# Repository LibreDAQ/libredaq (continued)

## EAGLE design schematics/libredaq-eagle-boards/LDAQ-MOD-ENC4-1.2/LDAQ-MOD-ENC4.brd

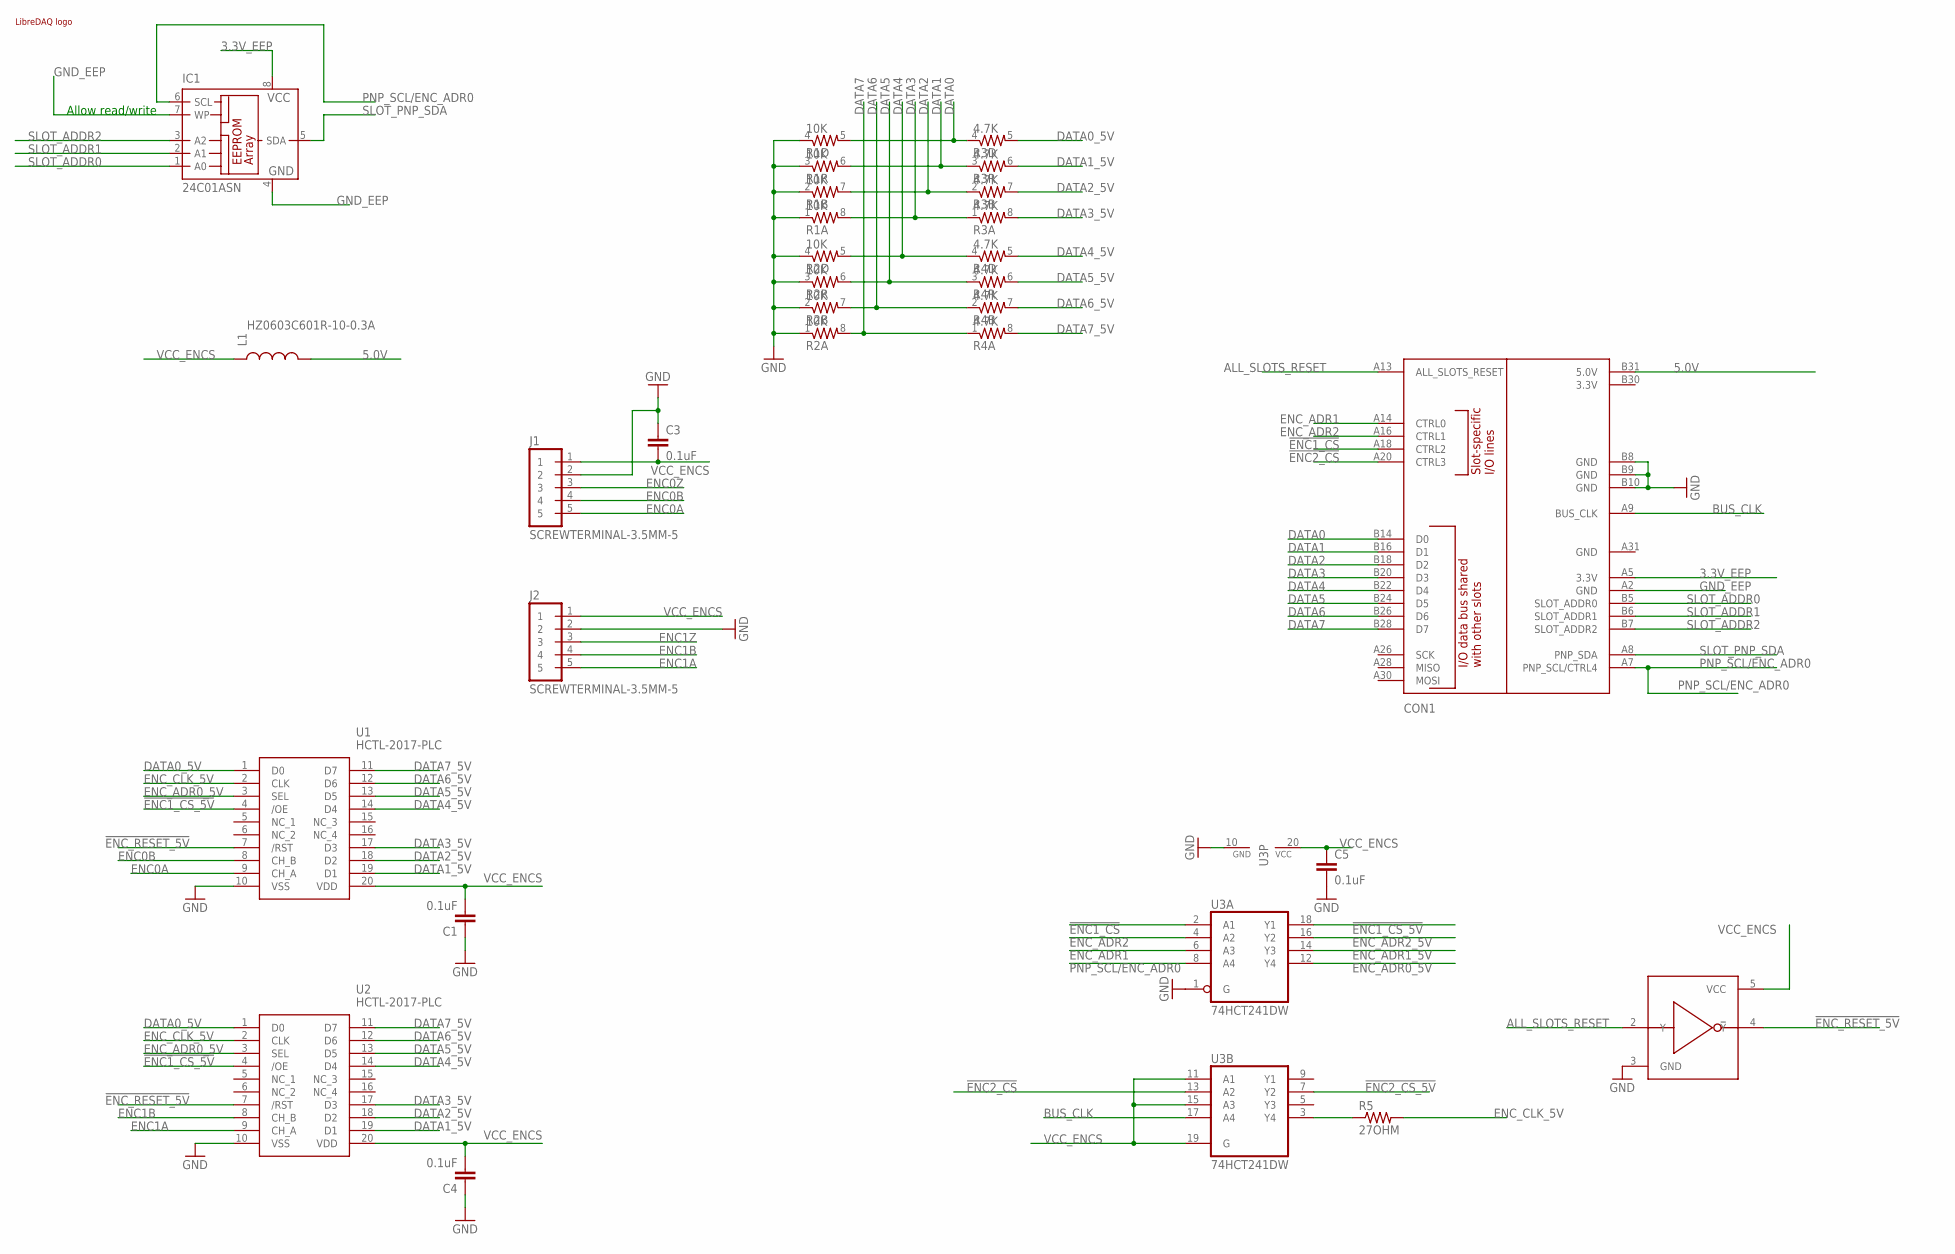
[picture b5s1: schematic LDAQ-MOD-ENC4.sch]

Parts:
C1, C3, C4, C5: 0.1uF; 0603-CAP
CON1: BOARD; PCI-E_64_EDGE_70X60_PADS-ONLY
IC1: 24C01ASN; SO-08
J1, J2: SCREWTERMINAL-3.5MM-5
L1: HZ0603C601R-10-0.3A; 0603
LOGO1: LIBREDAQ_LOGO_MINILOGO_GENERIC; LIBREDAQ_LOGO
R1, R2: 10K; 0603-ARV
R3, R4: 4.7K; 0603-ARV
R5: 27OHM; 0603
U1, U2: HCTL-2017-PLC; PLCC127P991X991X457-20N
U3: 74HCT241DW; SO20W
U4: 74AHCT1G04; SOT353-SC70-5

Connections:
3.3V_EEP: CON1.A5 (3.3V), IC1.8 (VCC)
5.0V: CON1.B31 (5.0V), L1.2
!ENC1_CS: CON1.A18 (CTRL2), U3.2 (A1)
!ENC1_CS_5V: U1.4 (/OE), U2.4 (/OE), U3.18 (Y1)
!ENC2_CS: CON1.A20 (CTRL3), U3.13 (A2)
!ENC2_CS_5V: U3.7 (Y2)
!ENC_RESET_5V: U1.7 (/RST), U2.7 (/RST), U4.4 (!Y)
ALL_SLOTS_RESET: CON1.A13 (ALL_SLOTS_RESET), U4.2 (Y)
BUS_CLK: CON1.A9 (BUS_CLK), U3.17 (A4)
DATA0: CON1.B14 (D0), R1.5 (2), R3.4 (1)
DATA0_5V: R3.5 (2), U1.1 (D0), U2.1 (D0)
DATA1: CON1.B16 (D1), R1.6 (2), R3.3 (1)
DATA1_5V: R3.6 (2), U1.19 (D1), U2.19 (D1)
DATA2: CON1.B18 (D2), R1.7 (2), R3.2 (1)
DATA2_5V: R3.7 (2), U1.18 (D2), U2.18 (D2)
DATA3: CON1.B20 (D3), R1.8 (2), R3.1
DATA3_5V: R3.8 (2), U1.17 (D3), U2.17 (D3)
DATA4: CON1.B22 (D4), R2.5 (2), R4.4 (1)
DATA4_5V: R4.5 (2), U1.14 (D4), U2.14 (D4)
DATA5: CON1.B24 (D5), R2.6 (2), R4.3 (1)
DATA5_5V: R4.6 (2), U1.13 (D5), U2.13 (D5)
DATA6: CON1.B26 (D6), R2.7 (2), R4.2 (1)
DATA6_5V: R4.7 (2), U1.12 (D6), U2.12 (D6)
DATA7: CON1.B28 (D7), R2.8 (2), R4.1
DATA7_5V: R4.8 (2), U1.11 (D7), U2.11 (D7)
ENC0A: J1.5, U1.9 (CH_A)
ENC0B: J1.4, U1.8 (CH_B)
ENC0Z: J1.3
ENC1A: J2.5, U2.9 (CH_A)
ENC1B: J2.4, U2.8 (CH_B)
ENC1Z: J2.3
ENC_ADR0_5V: U1.3 (SEL), U2.3 (SEL), U3.12 (Y4)
ENC_ADR1: CON1.A14 (CTRL0), U3.6 (A3)
ENC_ADR1_5V: U3.14 (Y3)
ENC_ADR2: CON1.A16 (CTRL1), U3.4 (A2)
ENC_ADR2_5V: U3.16 (Y2)
ENC_CLK_5V: R5.2, U1.2 (CLK), U2.2 (CLK)
GND: C1.1, C3.1, C4.1, C5.2, CON1.B8 (GND), CON1.B9 (GND), CON1.B10 (GND), J1.2, J2.2, R1.1, R1.2 (1), R1.3 (1), R1.4 (1), R2.1, R2.2 (1), R2.3 (1), R2.4 (1), U1.10 (VSS), U2.10 (VSS), U3.1 (G), U3.10 (GND), U4.3 (GND)
GND_EEP: CON1.A2 (GND), IC1.4 (GND), IC1.7 (WP)
unnamed: R5.1, U3.3 (Y4)
PNP_SCL/ENC_ADR0: CON1.A7 (PNP_SCL/CTRL4), IC1.6 (SCL), U3.8 (A4)
SLOT_ADDR0: CON1.B5 (SLOT_ADDR0), IC1.1 (A0)
SLOT_ADDR1: CON1.B6 (SLOT_ADDR1), IC1.2 (A1)
SLOT_ADDR2: CON1.B7 (SLOT_ADDR2), IC1.3 (A2)
SLOT_PNP_SDA: CON1.A8 (PNP_SDA), IC1.5 (SDA)
VCC_ENCS: C1.2, C3.2, C4.2, C5.1, J1.1, J2.1, L1.1, U1.20 (VDD), U2.20 (VDD), U3.11 (A1), U3.15 (A3), U3.19 (G), U3.20 (VCC), U4.5 (VCC)

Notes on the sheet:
Allow read/write

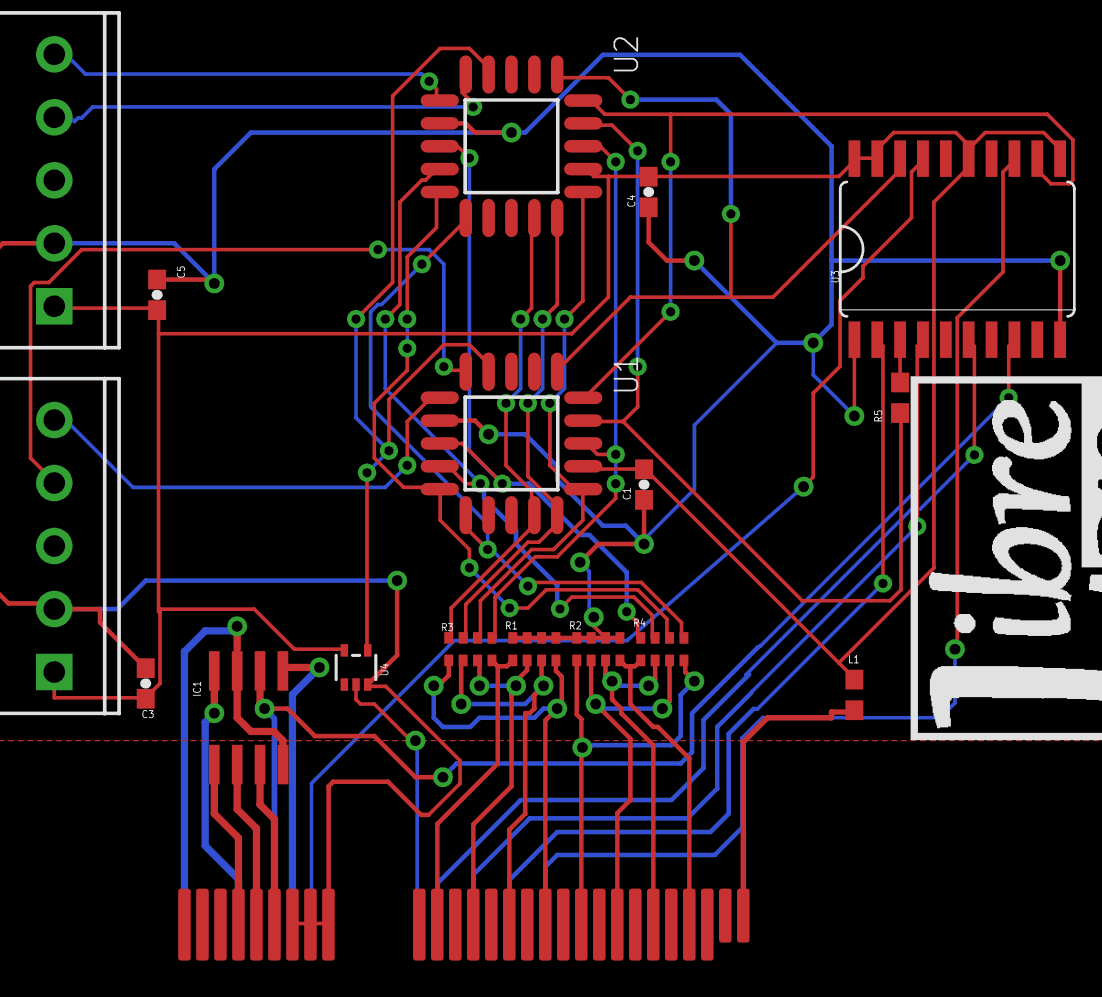
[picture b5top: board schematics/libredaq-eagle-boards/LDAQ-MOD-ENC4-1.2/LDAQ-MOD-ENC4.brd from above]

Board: 2 copper layers, 19 parts (0 on the bottom side), 41 nets.

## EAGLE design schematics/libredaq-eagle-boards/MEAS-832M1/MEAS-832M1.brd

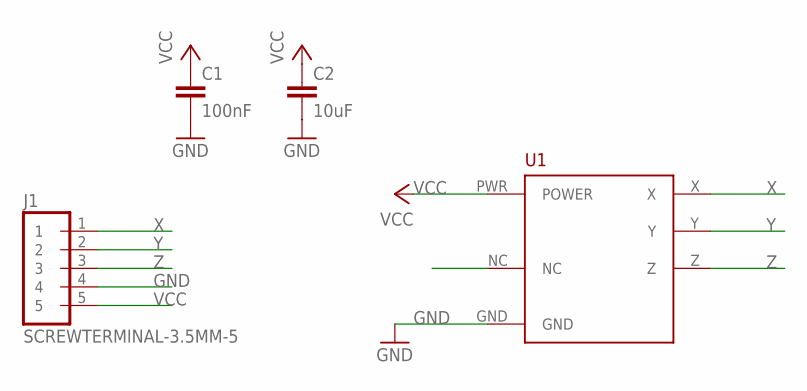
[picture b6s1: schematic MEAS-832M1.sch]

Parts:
C1: 100nF; C0805K
C2: 10uF; C0805K
J1: SCREWTERMINAL-3.5MM-5
U1: MEAS-832M1

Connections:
GND: C1.2, C2.2, J1.4, U1.GND
VCC: C1.1, C2.1, J1.5, U1.PWR (POWER)
X: J1.1, U1.X
Y: J1.2, U1.Y
Z: J1.3, U1.Z

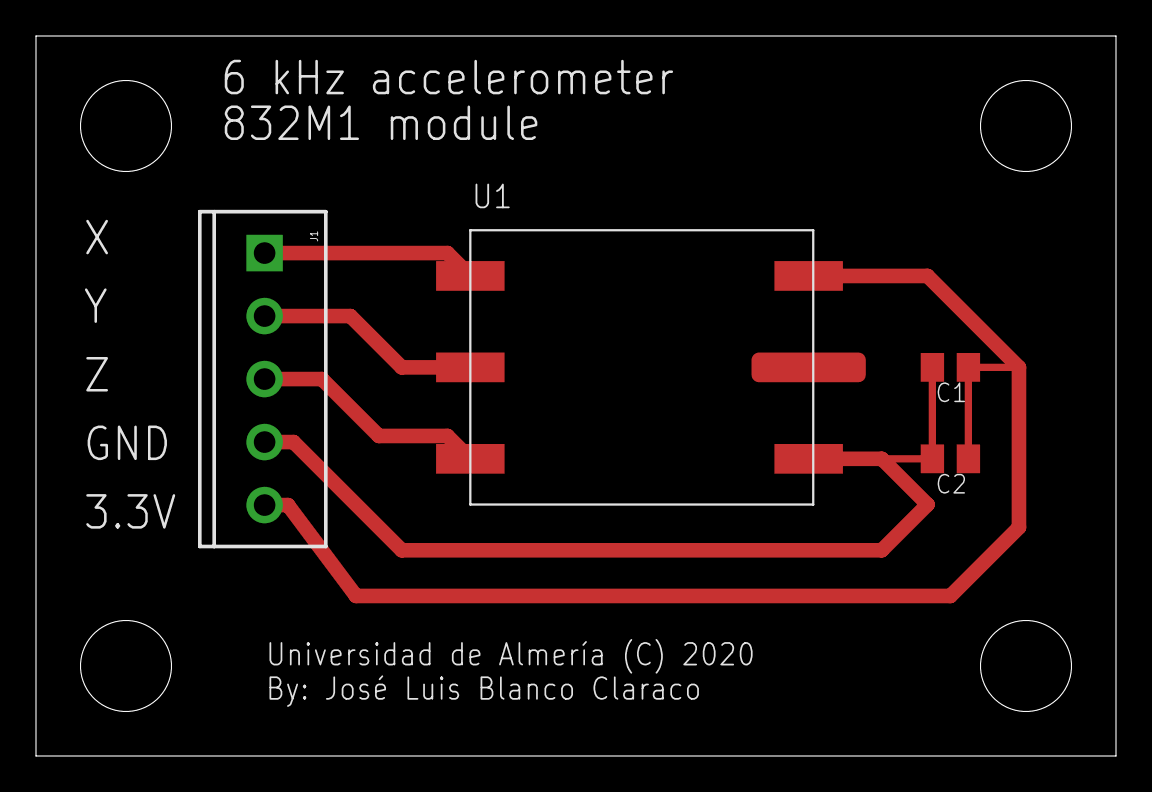
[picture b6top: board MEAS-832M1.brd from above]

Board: 2 copper layers, 60.0 x 40.0 mm, 4 parts (0 on the bottom side), 5 nets.

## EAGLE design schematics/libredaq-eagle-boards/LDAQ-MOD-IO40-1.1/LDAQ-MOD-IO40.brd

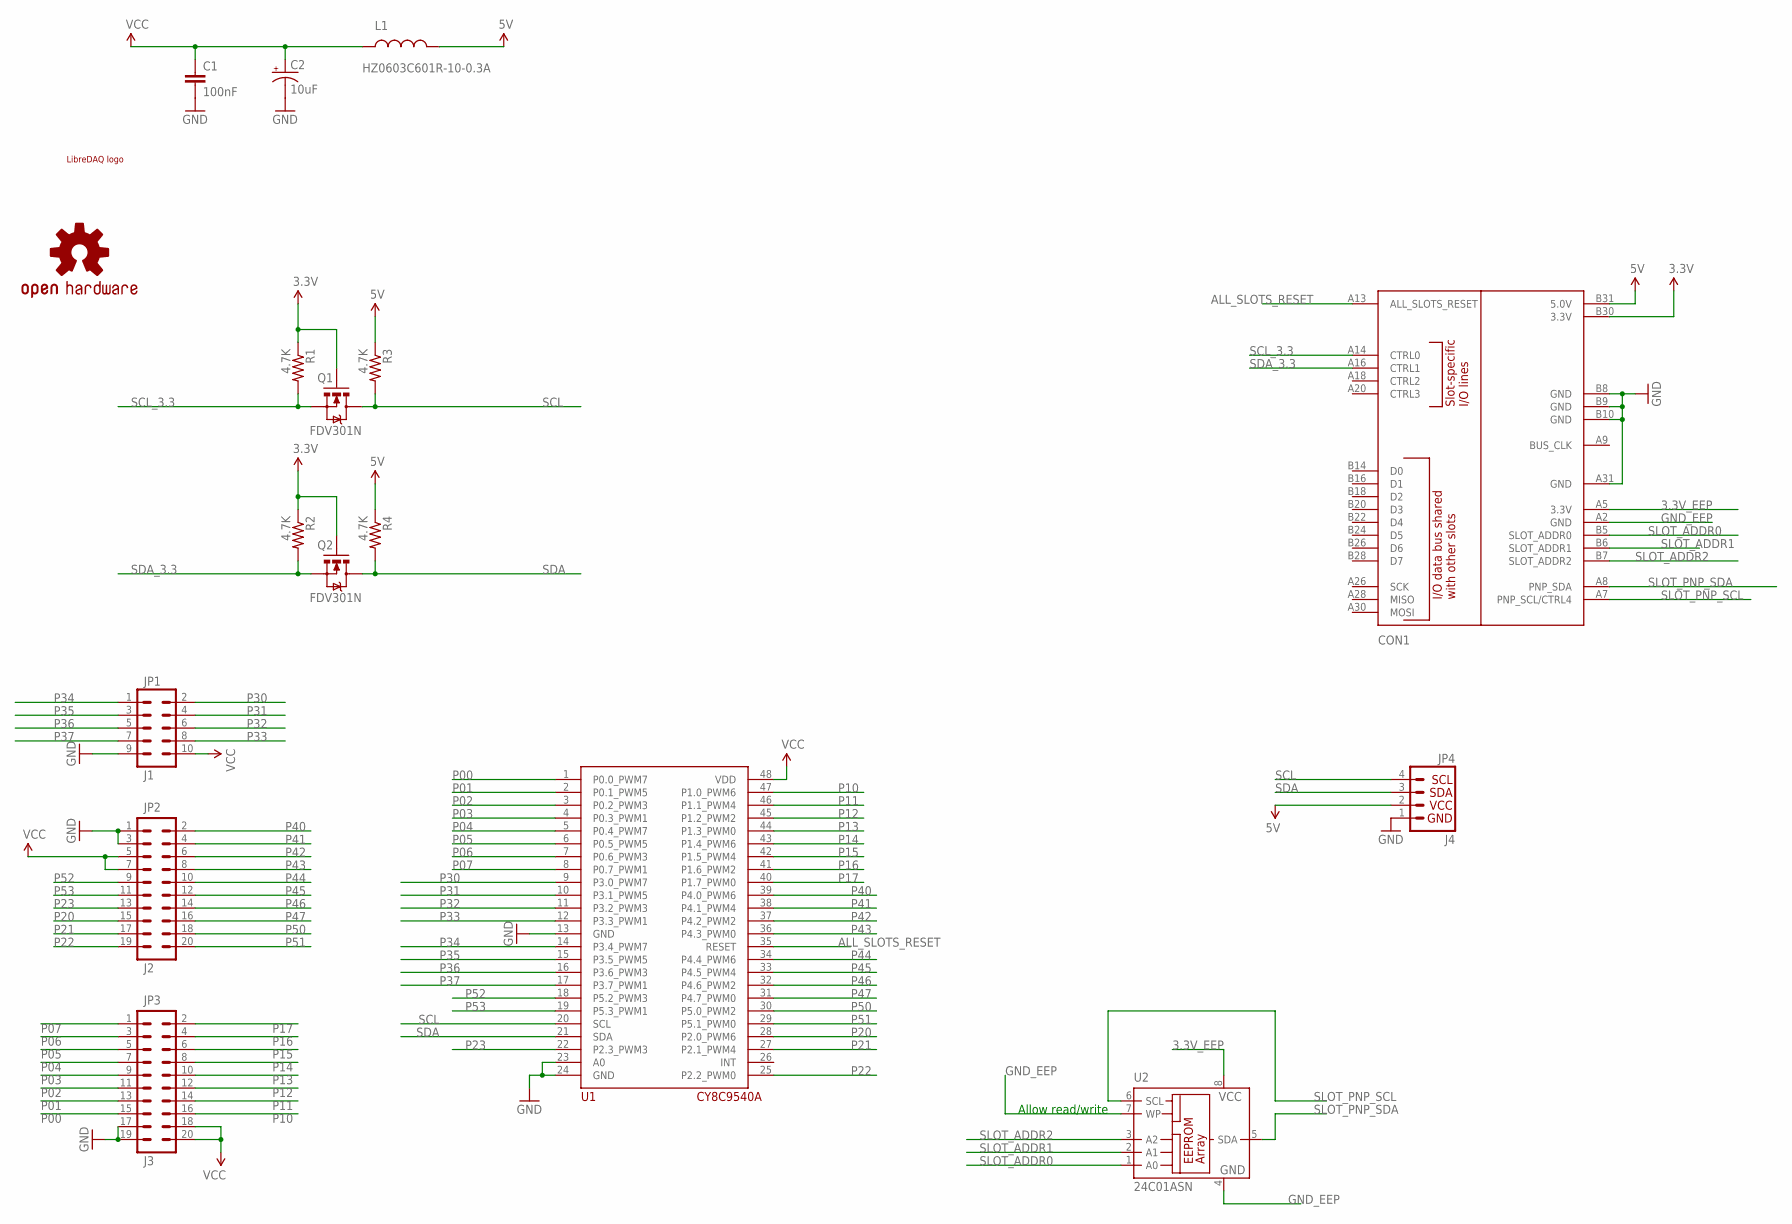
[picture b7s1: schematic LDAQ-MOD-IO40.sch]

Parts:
C1: 100nF; 0603-CAP
C2: 10uF; EIA3216
CON1: C1; PCI-E_64_EDGE_70X60_PADS-ONLY
JP1: J1; 2X5-SHROUDED
JP2: J2; 2X10-SHROUDED
JP3: J3; 2X10-SHROUDED
JP4: J4; 1X04
L1: HZ0603C601R-10-0.3A; 0603
LOGO1: LIBREDAQ_LOGO_MINILOGO_GENERIC; LIBREDAQ_LOGO
LOGO2: OSHW-LOGOM; OSHW-LOGO-M
Q1, Q2: FDV301N; SOT23-3
R1, R2, R3, R4: 4.7K; 0603-RES
U1: CY8C9540A; SSOP-48
U2: 24C01ASN; SO-08

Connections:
3.3V: CON1.B30 (3.3V), Q1.1 (G), Q2.1 (G), R1.1, R2.1
3.3V_EEP: CON1.A5 (3.3V), U2.8 (VCC)
5V: CON1.B31 (5.0V), JP4.2, L1.2, R3.1, R4.1
ALL_SLOTS_RESET: CON1.A13 (ALL_SLOTS_RESET), U1.35 (RESET)
GND: C1.2, C2.C (-), CON1.A31 (GND), CON1.B8 (GND), CON1.B9 (GND), CON1.B10 (GND), JP1.9, JP2.1, JP2.3, JP3.17, JP3.19, JP4.1, U1.13 (GND), U1.23 (A0), U1.24 (GND)
GND_EEP: CON1.A2 (GND), U2.4 (GND), U2.7 (WP)
P00: JP3.15, U1.1 (P0.0_PWM7)
P01: JP3.13, U1.2 (P0.1_PWM5)
P02: JP3.11, U1.3 (P0.2_PWM3)
P03: JP3.9, U1.4 (P0.3_PWM1)
P04: JP3.7, U1.5 (P0.4_PWM7)
P05: JP3.5, U1.6 (P0.5_PWM5)
P06: JP3.3, U1.7 (P0.6_PWM3)
P07: JP3.1, U1.8 (P0.7_PWM1)
P10: JP3.16, U1.47 (P1.0_PWM6)
P11: JP3.14, U1.46 (P1.1_PWM4)
P12: JP3.12, U1.45 (P1.2_PWM2)
P13: JP3.10, U1.44 (P1.3_PWM0)
P14: JP3.8, U1.43 (P1.4_PWM6)
P15: JP3.6, U1.42 (P1.5_PWM4)
P16: JP3.4, U1.41 (P1.6_PWM2)
P17: JP3.2, U1.40 (P1.7_PWM0)
P20: JP2.15, U1.28 (P2.0_PWM6)
P21: JP2.17, U1.27 (P2.1_PWM4)
P22: JP2.19, U1.25 (P2.2_PWM0)
P23: JP2.13, U1.22 (P2.3_PWM3)
P30: JP1.2, U1.9 (P3.0_PWM7)
P31: JP1.4, U1.10 (P3.1_PWM5)
P32: JP1.6, U1.11 (P3.2_PWM3)
P33: JP1.8, U1.12 (P3.3_PWM1)
P34: JP1.1, U1.14 (P3.4_PWM7)
P35: JP1.3, U1.15 (P3.5_PWM5)
P36: JP1.5, U1.16 (P3.6_PWM3)
P37: JP1.7, U1.17 (P3.7_PWM1)
P40: JP2.2, U1.39 (P4.0_PWM6)
P41: JP2.4, U1.38 (P4.1_PWM4)
P42: JP2.6, U1.37 (P4.2_PWM2)
P43: JP2.8, U1.36 (P4.3_PWM0)
P44: JP2.10, U1.34 (P4.4_PWM6)
P45: JP2.12, U1.33 (P4.5_PWM4)
P46: JP2.14, U1.32 (P4.6_PWM2)
P47: JP2.16, U1.31 (P4.7_PWM0)
P50: JP2.18, U1.30 (P5.0_PWM2)
P51: JP2.20, U1.29 (P5.1_PWM0)
P52: JP2.9, U1.18 (P5.2_PWM3)
P53: JP2.11, U1.19 (P5.3_PWM1)
SCL: JP4.4, Q1.3 (D), R3.2, U1.20 (SCL)
SCL_3.3: CON1.A14 (CTRL0), Q1.2 (S), R1.2
SDA: JP4.3, Q2.3 (D), R4.2, U1.21 (SDA)
SDA_3.3: CON1.A16 (CTRL1), Q2.2 (S), R2.2
SLOT_ADDR0: CON1.B5 (SLOT_ADDR0), U2.1 (A0)
SLOT_ADDR1: CON1.B6 (SLOT_ADDR1), U2.2 (A1)
SLOT_ADDR2: CON1.B7 (SLOT_ADDR2), U2.3 (A2)
SLOT_PNP_SCL: CON1.A7 (PNP_SCL/CTRL4), U2.6 (SCL)
SLOT_PNP_SDA: CON1.A8 (PNP_SDA), U2.5 (SDA)
VCC: C1.1, C2.A (+), JP1.10, JP2.5, JP2.7, JP3.18, JP3.20, L1.1, U1.48 (VDD)

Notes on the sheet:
Allow read/write

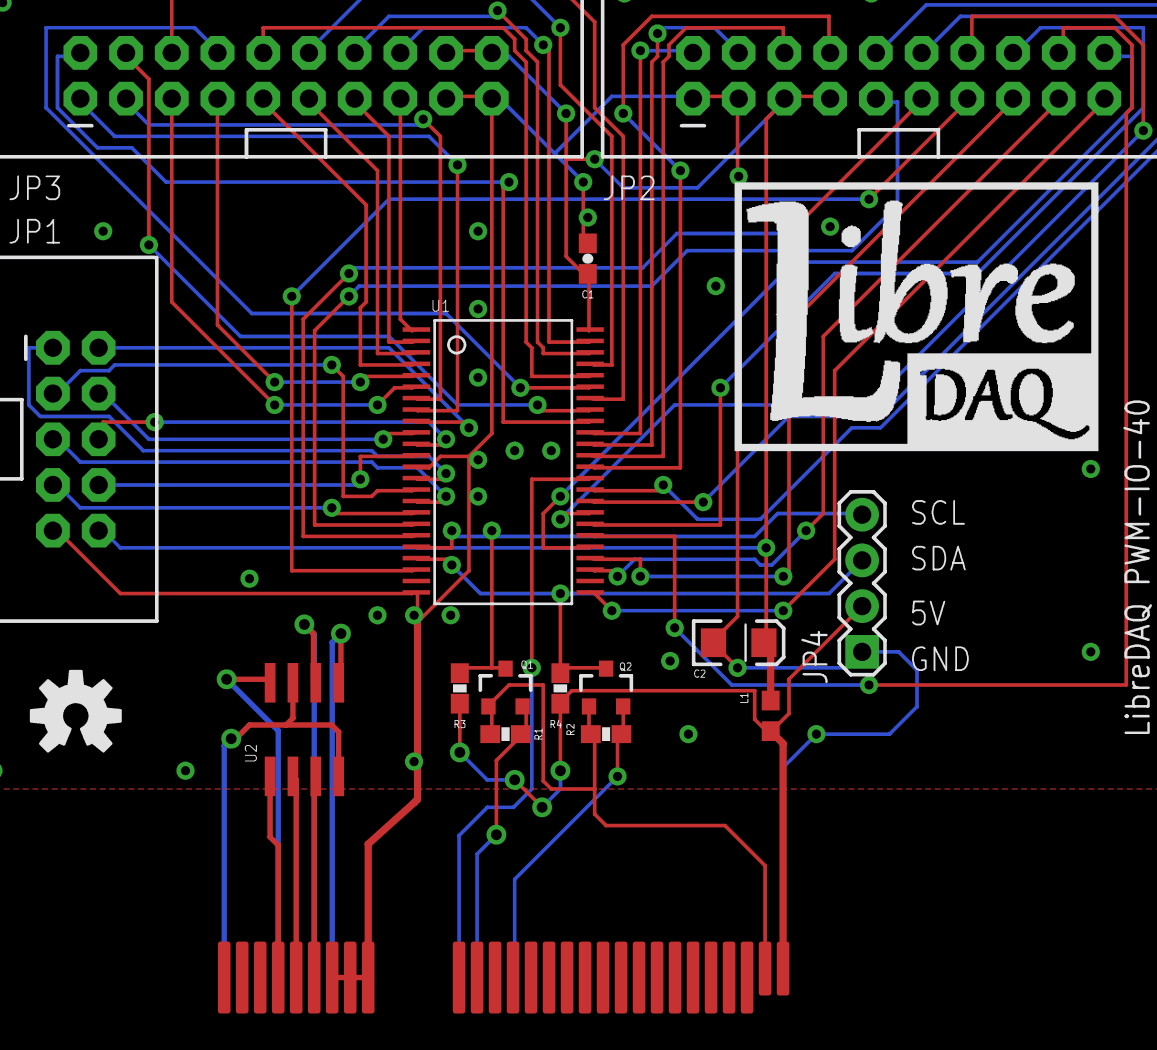
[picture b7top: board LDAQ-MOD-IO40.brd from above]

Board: 2 copper layers, 18 parts (0 on the bottom side), 56 nets.

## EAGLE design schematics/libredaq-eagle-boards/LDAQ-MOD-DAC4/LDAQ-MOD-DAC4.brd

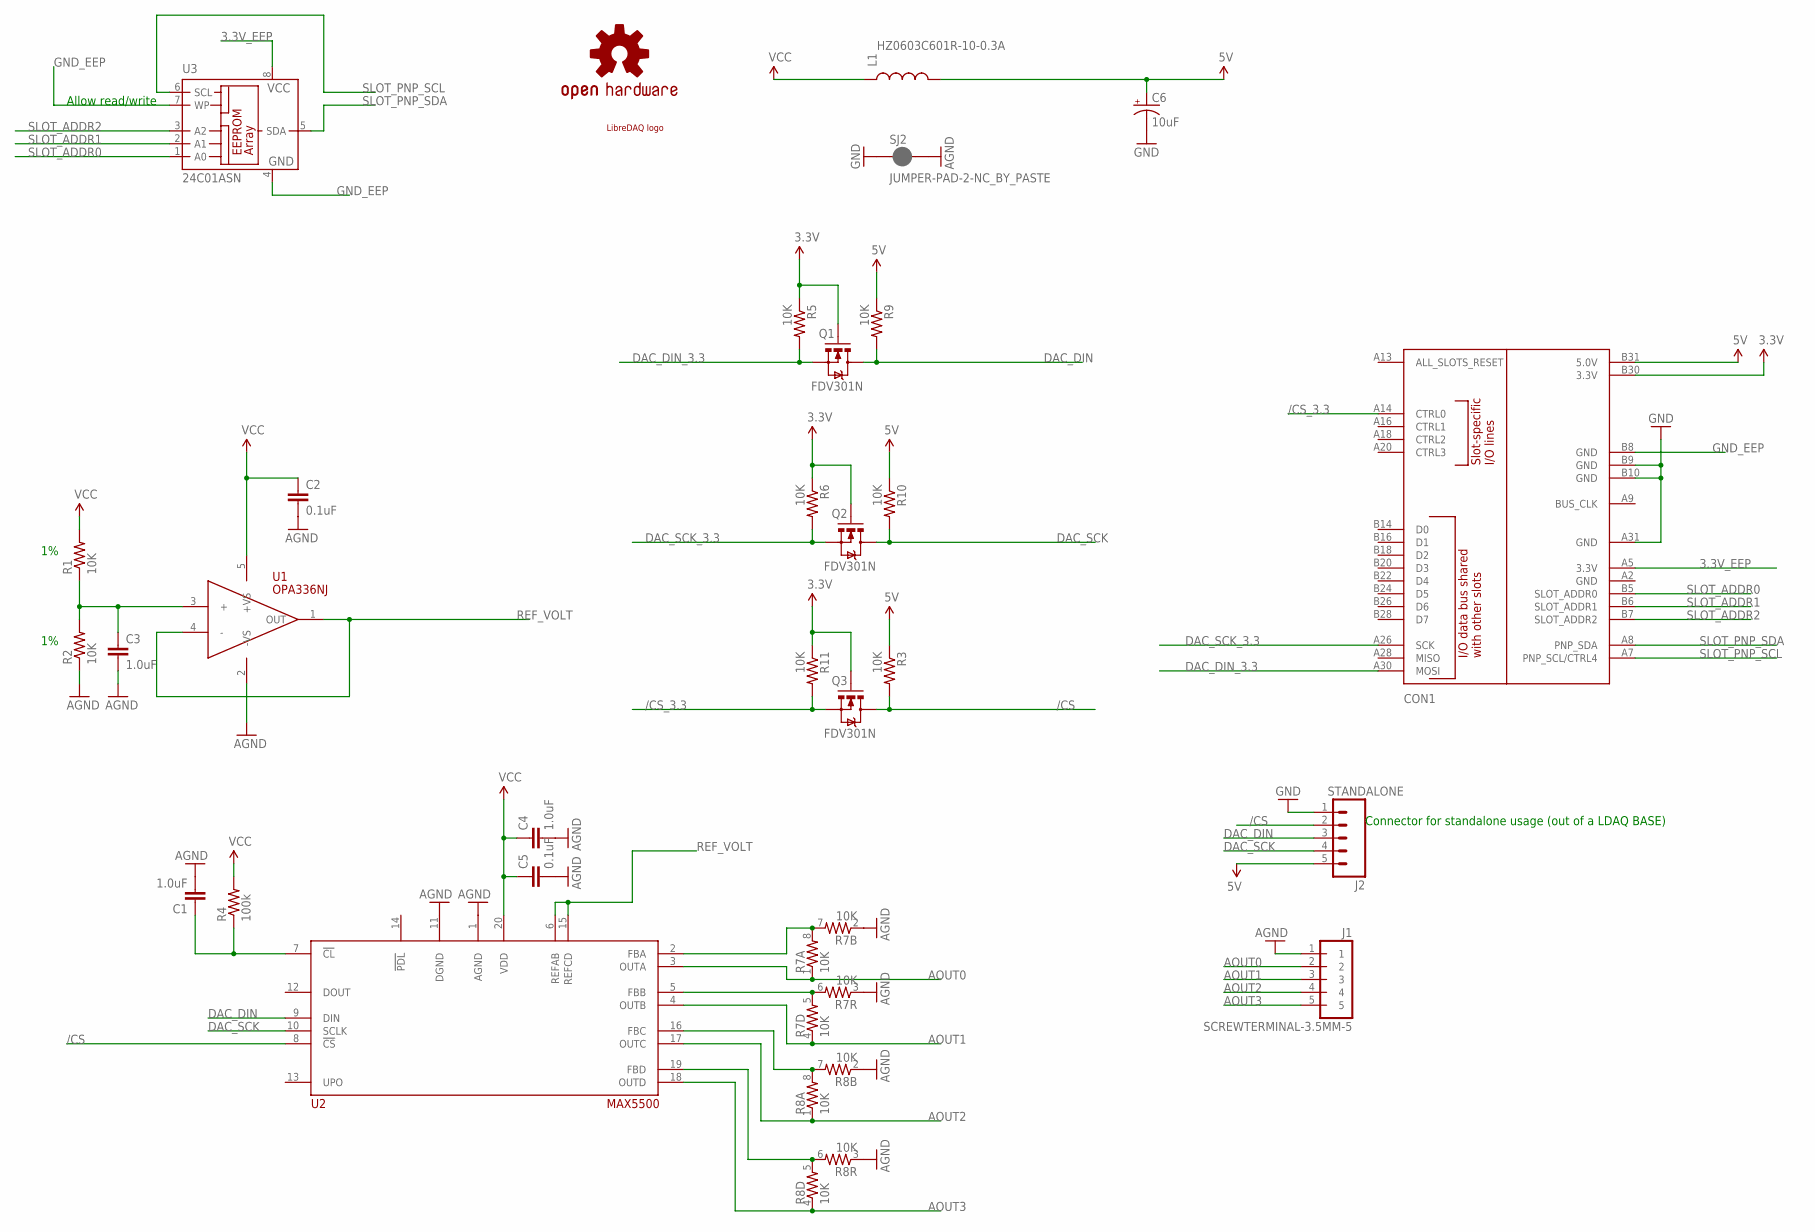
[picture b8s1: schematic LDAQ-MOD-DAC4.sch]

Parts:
C1, C3, C4: 1.0uF; 0603-CAP
C2, C5: 0.1uF; 0603-CAP
C6: 10uF; EIA3216
CON1: BOARD; PCI-E_64_EDGE_63X50_PADS-ONLY
J1: SCREWTERMINAL-3.5MM-5
J2: STANDALONE; 1X05_LOCK
L1: HZ0603C601R-10-0.3A; 0603
LOGO1: OSHW-LOGOL; OSHW-LOGO-L
Q1, Q2, Q3: FDV301N; SOT23-3
R1, R2, R3, R5, R6, R9, R10, R11: 10K; 0603-RES
R4: 100k; 0603-RES
R7, R8: 10K; 0603-ARV
SJ2: JUMPER-PAD-2-NC_BY_PASTE; PAD-JUMPER-2-NC_BY_PASTE_YES_SILK
U1: OPA336NJ; SOT23-5
U2: MAX5500; SSOP20
U3: 24C01ASN; SO-08
U$1: LIBREDAQ_LOGO_MINILOGO_GENERIC; LIBREDAQ_LOGO

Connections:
3.3V: CON1.B30 (3.3V), Q1.1 (G), Q2.1 (G), Q3.1 (G), R5.1, R6.1, R11.1
3.3V_EEP: CON1.A5 (3.3V), U3.8 (VCC)
5V: C6.A (+), CON1.B31 (5.0V), J2.5, L1.2, R3.1, R9.1, R10.1
/CS: J2.2, Q3.3 (D), R3.2, U2.8 (!CS)
/CS_3.3: CON1.A14 (CTRL0), Q3.2 (S), R11.2
AGND: C1.2, C2.2, C3.2, C4.2, C5.2, J1.1, R2.1, R7.2 (1), R7.3 (1), R8.2 (1), R8.3 (1), SJ2.2, U1.2 (-VS), U2.1 (AGND), U2.11 (DGND)
AOUT0: J1.2, R7.1, U2.3 (OUTA)
AOUT1: J1.3, R7.4 (1), U2.4 (OUTB)
AOUT2: J1.4, R8.1, U2.17 (OUTC)
AOUT3: J1.5, R8.4 (1), U2.18 (OUTD)
DAC_DIN: J2.3, Q1.3 (D), R9.2, U2.9 (DIN)
DAC_DIN_3.3: CON1.A30 (MOSI), Q1.2 (S), R5.2
DAC_SCK: J2.4, Q2.3 (D), R10.2, U2.10 (SCLK)
DAC_SCK_3.3: CON1.A26 (SCK), Q2.2 (S), R6.2
GND: C6.C (-), CON1.A31 (GND), CON1.B9 (GND), CON1.B10 (GND), J2.1, SJ2.1
GND_EEP: CON1.B8 (GND), U3.4 (GND), U3.7 (WP)
unnamed: R7.7 (2), R7.8 (2), U2.2 (FBA)
unnamed: C1.1, R4.1, U2.7 (!CL)
unnamed: R7.5 (2), R7.6 (2), U2.5 (FBB)
unnamed: R8.7 (2), R8.8 (2), U2.16 (FBC)
unnamed: R8.5 (2), R8.6 (2), U2.19 (FBD)
unnamed: C3.1, R1.1, R2.2, U1.3 (+)
REF_VOLT: U1.1 (OUT), U1.4 (-), U2.6 (REFAB), U2.15 (REFCD)
SLOT_ADDR0: CON1.B5 (SLOT_ADDR0), U3.1 (A0)
SLOT_ADDR1: CON1.B6 (SLOT_ADDR1), U3.2 (A1)
SLOT_ADDR2: CON1.B7 (SLOT_ADDR2), U3.3 (A2)
SLOT_PNP_SCL: CON1.A7 (PNP_SCL/CTRL4), U3.6 (SCL)
SLOT_PNP_SDA: CON1.A8 (PNP_SDA), U3.5 (SDA)
VCC: C2.1, C4.1, C5.1, L1.1, R1.2, R4.2, U1.5 (+VS), U2.20 (VDD)

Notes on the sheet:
Allow read/write
Connector for standalone usage (out of a LDAQ BASE)

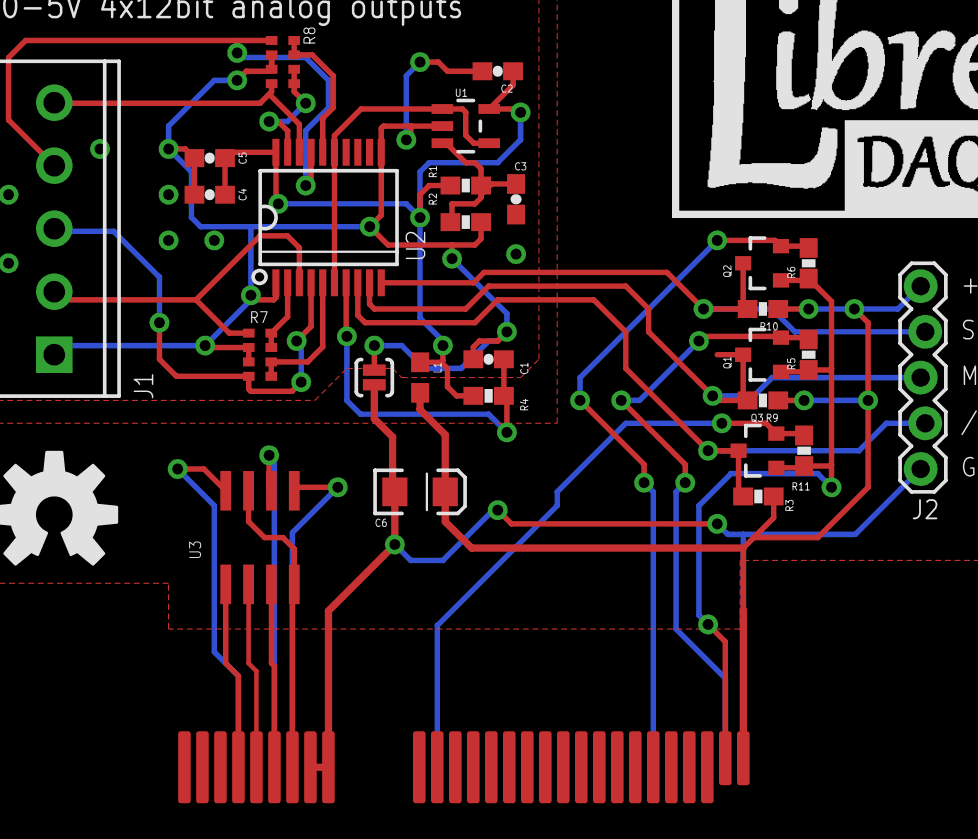
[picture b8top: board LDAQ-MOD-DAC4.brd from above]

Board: 2 copper layers, 30 parts (0 on the bottom side), 29 nets.

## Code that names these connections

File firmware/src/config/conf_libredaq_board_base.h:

/*+-------------------------------------------------------------------------+
  |                             LibreDAQ                                    |
  |                                                                         |
  | Copyright (C) 2015  Jose Luis Blanco Claraco                            |
  | Distributed under GNU General Public License version 3                  |
  |   See <http://www.gnu.org/licenses/>                                    |
  +-------------------------------------------------------------------------+  */

 /* This file is intended to contain definitions and configuration details for
 * features and devices that are available on the board, e.g., frequency and
 * startup time for an external crystal, external memory devices, LED and USART
 * pins.
 */
#pragma once

// On-board LEDs --------------------
#define LED1_GPIO    PIO_PA27_IDX
#define LED2_GPIO    PIO_PB13_IDX

// Include all HW & SW to handle the parallel bus to pluggable slots:
#define HAVE_LDAQ_SLOT_BUS     1  // Yes

// 8-bit PARALLEL BUS
#define LDAQ_PARALLEL_BUS_PIO  PIOA
#define LDAQ_PARALLEL_BUS_PINS  0x00ff
// Use to read the 8bit parallel bus pins
#define LDAQ_READ_PARALLEL_BUS  (LDAQ_PARALLEL_BUS_PIO->PIO_PDSR & LDAQ_PARALLEL_BUS_PINS)

// LDAQ_RESET (global to all slots) = PA12
#define LDAQ_ALL_SLOTS_RESET_GPIO  PIO_PA12_IDX

// I2C BUS for PnP detection of modules in SLOTs: SDA=PB21. SCL/CRTL4=PB22  
#define LDAQ_PNP_I2C_SDA_GPIO  PIO_PB21_IDX
#define LDAQ_PNP_I2C_SCL_GPIO  PIO_PB22_IDX
#define LDAQ_SLOTx_CTRL4_GPIO  PIO_PB22_IDX    // This control signal is shared among all slots.
#define LDAQ_SLOTx_CTRL4_PIO   PIOB
#define LDAQ_SLOTx_CTRL4_IDX   22

// Common programmable clock to all slots: PB24 / PCK1
#define LDAQ_SLOTS_PCLK_PMC_PCK   PMC_PCK_1
#define LDAQ_SLOTS_PCLK_GPIO      PIO_PB24_IDX
#define LDAQ_SLOTS_PCLK_PIO       PIOB
#define LDAQ_SLOTS_PCLK_IDX       24

// Common SPI bus to all slots: TXD2(PA22), RXD2(PA23), SCK2(PA25)
#define LDAQ_SLOTS_SPI_USART         USART2
#define LDAQ_SLOTS_SPI_ID_USART      ID_USART2
#define LDAQ_SLOTS_SPI_BAUDRATE      10000000u   // (CKL freq, in Hz)

#define LDAQ_SLOTS_SPI_TXD_PIO       PIOA
#define LDAQ_SLOTS_SPI_TXD_IDX       22
#define LDAQ_SLOTS_SPI_TXD_PERIP     PIO_PERIPH_A

#define LDAQ_SLOTS_SPI_RXD_PIO       PIOA
#define LDAQ_SLOTS_SPI_RXD_IDX       23
#define LDAQ_SLOTS_SPI_RXD_PERIP     PIO_PERIPH_A

#define LDAQ_SLOTS_SPI_SCK_PIO       PIOA
#define LDAQ_SLOTS_SPI_SCK_IDX       25
#define LDAQ_SLOTS_SPI_SCK_PERIP     PIO_PERIPH_B



// SLOT 0 --------------
// SLOT0_CTRL0 = PA30
// SLOT0_CTRL1 = PB3
// SLOT0_CTRL2 = PB4
// SLOT0_CTRL3 = PA13
#define LDAQ_SLOT0_CTRL0_PIO  PIOA
#define LDAQ_SLOT0_CTRL0_IDX  30
#define LDAQ_SLOT0_CTRL0_GPIO PIO_PA30_IDX

#define LDAQ_SLOT0_CTRL1_PIO  PIOB
#define LDAQ_SLOT0_CTRL1_IDX  3
#define LDAQ_SLOT0_CTRL1_GPIO PIO_PB3_IDX
#define LDAQ_SLOT0_CTRL1_ID   ID_PIOB
#define LDAQ_SLOT0_CTRL1_IRQn PIOB_IRQn

#define LDAQ_SLOT0_CTRL2_PIO  PIOB
#define LDAQ_SLOT0_CTRL2_IDX  4
#define LDAQ_SLOT0_CTRL2_GPIO PIO_PB4_IDX
#define LDAQ_SLOT0_CTRL2_ID   ID_PIOB
#define LDAQ_SLOT0_CTRL2_IRQn PIOB_IRQn

#define LDAQ_SLOT0_CTRL3_PIO  PIOA
#define LDAQ_SLOT0_CTRL3_IDX  13
#define LDAQ_SLOT0_CTRL3_GPIO PIO_PA13_IDX

// SLOT 1 --------------
// SLOT1_CTRL0 = PA14
// SLOT1_CTRL1 = PA15
// SLOT1_CTRL2 = PA16
// SLOT1_CTRL3 = PA17
#define LDAQ_SLOT1_CTRL0_PIO  PIOA
#define LDAQ_SLOT1_CTRL0_IDX  14
#define LDAQ_SLOT1_CTRL0_GPIO PIO_PA14_IDX

#define LDAQ_SLOT1_CTRL1_PIO  PIOA
#define LDAQ_SLOT1_CTRL1_IDX  15
#define LDAQ_SLOT1_CTRL1_GPIO PIO_PA15_IDX
#define LDAQ_SLOT1_CTRL1_ID   ID_PIOA
#define LDAQ_SLOT1_CTRL1_IRQn PIOA_IRQn

#define LDAQ_SLOT1_CTRL2_PIO  PIOA
#define LDAQ_SLOT1_CTRL2_IDX  16
#define LDAQ_SLOT1_CTRL2_GPIO PIO_PA16_IDX
#define LDAQ_SLOT1_CTRL2_ID   ID_PIOA
#define LDAQ_SLOT1_CTRL2_IRQn PIOA_IRQn

#define LDAQ_SLOT1_CTRL3_PIO  PIOA
#define LDAQ_SLOT1_CTRL3_IDX  17
#define LDAQ_SLOT1_CTRL3_GPIO PIO_PA17_IDX

// SLOT 2 --------------
// SLOT2_CTRL0 = PA8
// SLOT2_CTRL1 = PA9
// SLOT2_CTRL2 = PA10
// SLOT2_CTRL3 = PA11
#define LDAQ_SLOT2_CTRL0_PIO  PIOA
#define LDAQ_SLOT2_CTRL0_IDX  8
#define LDAQ_SLOT2_CTRL0_GPIO PIO_PA8_IDX

#define LDAQ_SLOT2_CTRL1_PIO  PIOA
#define LDAQ_SLOT2_CTRL1_IDX  9
#define LDAQ_SLOT2_CTRL1_GPIO PIO_PA9_IDX
#define LDAQ_SLOT2_CTRL1_ID   ID_PIOA
#define LDAQ_SLOT2_CTRL1_IRQn PIOA_IRQn

#define LDAQ_SLOT2_CTRL2_PIO  PIOA
#define LDAQ_SLOT2_CTRL2_IDX  10
#define LDAQ_SLOT2_CTRL2_GPIO PIO_PA10_IDX
#define LDAQ_SLOT2_CTRL2_ID   ID_PIOA
#define LDAQ_SLOT2_CTRL2_IRQn PIOA_IRQn

#define LDAQ_SLOT2_CTRL3_PIO  PIOA
#define LDAQ_SLOT2_CTRL3_IDX  11
#define LDAQ_SLOT2_CTRL3_GPIO PIO_PA11_IDX

// SLOT 3 --------------
// SLOT3_CTRL0 = PB11
// SLOT3_CTRL1 = PB2
// SLOT3_CTRL2 = PB1
// SLOT3_CTRL3 = PB0
#define LDAQ_SLOT3_CTRL0_PIO  PIOB
#define LDAQ_SLOT3_CTRL0_IDX  11
#define LDAQ_SLOT3_CTRL0_GPIO PIO_PB11_IDX

#define LDAQ_SLOT3_CTRL1_PIO  PIOB
#define LDAQ_SLOT3_CTRL1_IDX  2
#define LDAQ_SLOT3_CTRL1_GPIO PIO_PB2_IDX
#define LDAQ_SLOT3_CTRL1_ID   ID_PIOB
#define LDAQ_SLOT3_CTRL1_IRQn PIOB_IRQn

#define LDAQ_SLOT3_CTRL2_PIO  PIOB
#define LDAQ_SLOT3_CTRL2_IDX  1
#define LDAQ_SLOT3_CTRL2_GPIO PIO_PB1_IDX
#define LDAQ_SLOT3_CTRL2_ID   ID_PIOB
#define LDAQ_SLOT3_CTRL2_IRQn PIOB_IRQn

#define LDAQ_SLOT3_CTRL3_PIO  PIOB
#define LDAQ_SLOT3_CTRL3_IDX  0
#define LDAQ_SLOT3_CTRL3_GPIO PIO_PB0_IDX

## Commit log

2015-03-02 First sketch of the lib structure
2015-03-03 Import a core set of utilities from mrpt
2015-03-03 format() refactor
2015-03-03 Normalize lib names (unix/win)
2015-03-03 Start of Device class
2015-03-11 Start ADC example
2015-03-12 First sort-of-working ADC example! :+1:
2015-03-12 ADC example: save to file
2015-03-15 Fix build in gcc
2015-06-02 Collect & show usb bandwidth stats
2015-06-06 Update of shared frames hdr; include processing of encoders
2015-06-06 More correct parsing of encoders
2015-06-09 Added the stop-all-tasks cmd
2015-06-10 Rename directory; added encoders example
2015-06-11 Synch frames header
2015-06-11 Add basic DAC cmds
2015-06-13 udev rules for Linux
2015-06-15 Support firmware modes cmd
2015-06-20 Added doxygen file
2015-06-20 clean gh-pages branch
2015-06-20 Scripts for dox docs
2015-06-20 First dox docs commit
2015-06-21 PGA-ADC is working
2015-06-21 Comms bug fixed
2015-06-27 Add driver for Windows
2015-06-28 Support for CMake FIND_PACKAGE()
2015-06-28 LibreDAQStudio: Basic cmake+qt setup
2015-06-28 Start LDStudio UI
2015-06-28 Fixes for cmake in linux
2015-07-05 Progress with UI
2015-07-06 UI update
2015-07-07 Remove un-needed file
2015-07-15 Timestamps passed to double
2015-07-15 New example: adc+encs. Data output format as double
2017-03-22 Import firmware from former repo
2018-05-29 Progress updating firmware
2018-06-01 Add build dirs to gitignore
2018-06-01 Update to latest ASF lib version
    All build now with AtmelStudio 7.0
2018-06-01 Change slot boards
    Slot 0: ADC. AD7606 module
    Slot 1: DAC. MAX5500 module
    Slot 2: Encoders.
2018-06-01 Add ROS node for Encoders
2018-08-16 Add board schematics
2018-08-16 Add schematic License
2018-08-16 Add bibtex ref and videos
2019-10-31 fix reading at high speed
2019-12-02 Add 832M1 sensor board
2019-12-02 add new encoders module with non-obsolete chip
2021-01-18 Upload figures
2021-01-18 update from local copy
2021-01-18 base board: use bidirectional 3.3-5V driver
2021-01-18 Base: Use JTAG 50mils connector
2021-02-21 Update connectors in BASE
2021-02-21 optimized board size
2021-02-21 more missing components in circuithub
2021-03-21 Revision with CPLD (TODO: rewire)
2021-05-26 update adc8 board
2021-05-26 done with adc8 board
2021-09-21 Start upgrade to another FPGA
2021-09-30 New accelerometer board
2021-09-30 update board
2021-12-30 upgrade ASF version
2022-01-08 Restart new firmware
2022-02-18 fixed linker memory map for ATSAM3U1CB
2022-02-18 dont ignore linker script git changes!
2022-02-18 remove old files
2022-02-18 new firmware again
2022-02-18 fix ram size
2022-02-18 Import part of old firmware
2022-02-18 new firmware builds
2022-02-18 update main
2022-04-18 clang-format to all code
2022-04-19 Modernize C++ code
2022-04-19 gitignore update
2022-04-19 remove attempt to new firmware
2022-04-19 restore old working firmware
2022-04-19 clean up and notes
2022-04-19 fix windows build; adc to slot 0
2022-04-19 clean up
2022-10-17 expose format()
